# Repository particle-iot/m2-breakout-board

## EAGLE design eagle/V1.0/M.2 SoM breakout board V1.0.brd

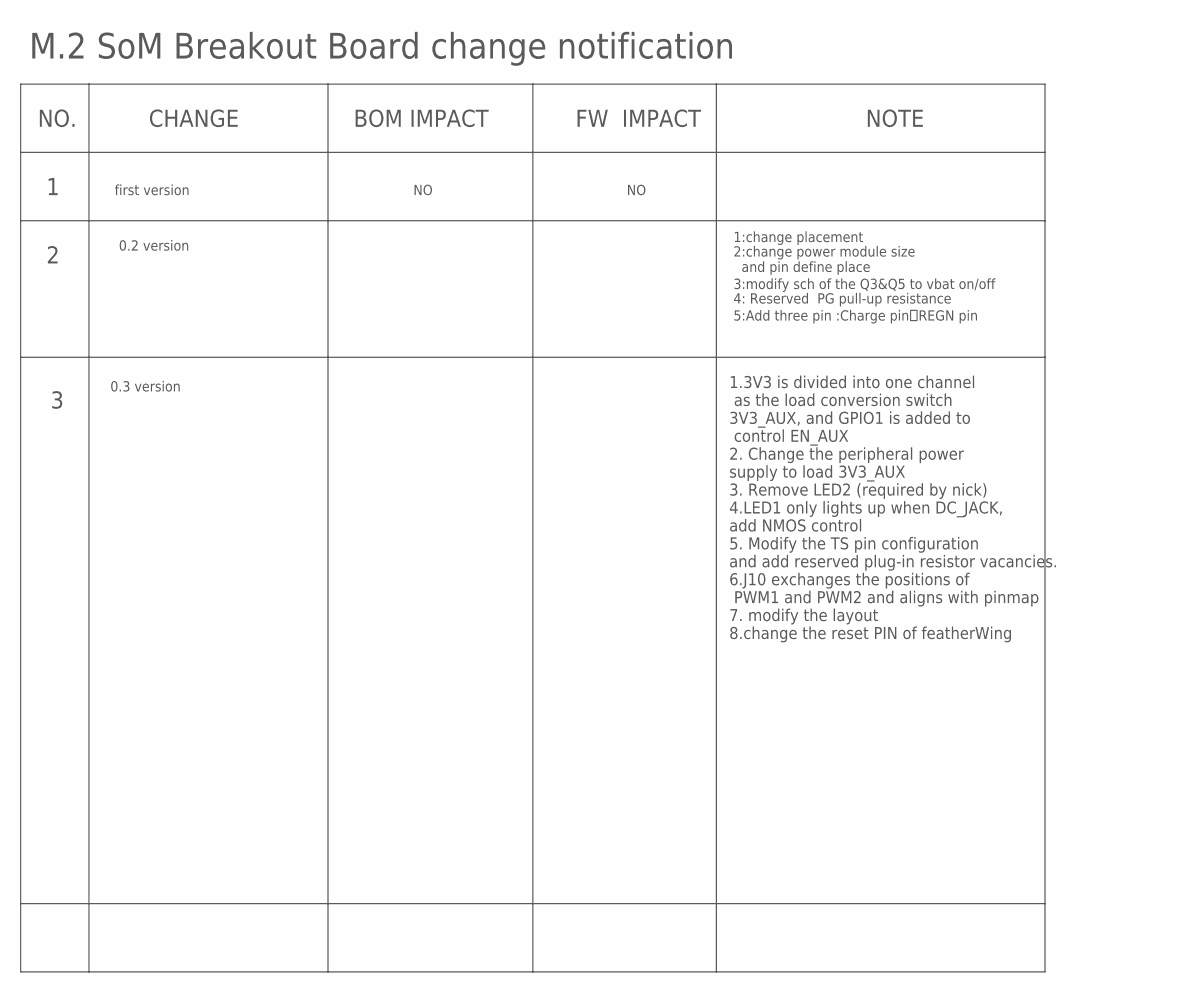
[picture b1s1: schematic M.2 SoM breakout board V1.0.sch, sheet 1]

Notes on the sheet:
NO.
CHANGE
BOM IMPACT
FW IMPACT
NOTE
first version
M.2 SoM Breakout Board change notification
0.2 version
1:change placement
3:modify sch of the Q3&Q5 to vbat on/off
5:Add three pin :Charge pin，REGN pin
2:change power module size and pin define place
4: Reserved PG pull-up resistance
0.3 version
1.3V3 is divided into one channel as the load conversion switch 3V3_AUX, and GPIO1 is added to control EN_AUX 2. Change the peripheral power supply to load 3V3_AUX 3. Remove LED2 (required by nick) 4.LED1 only lights up when DC_JACK, add NMOS control 5. Modify the TS pin configuration and add reser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

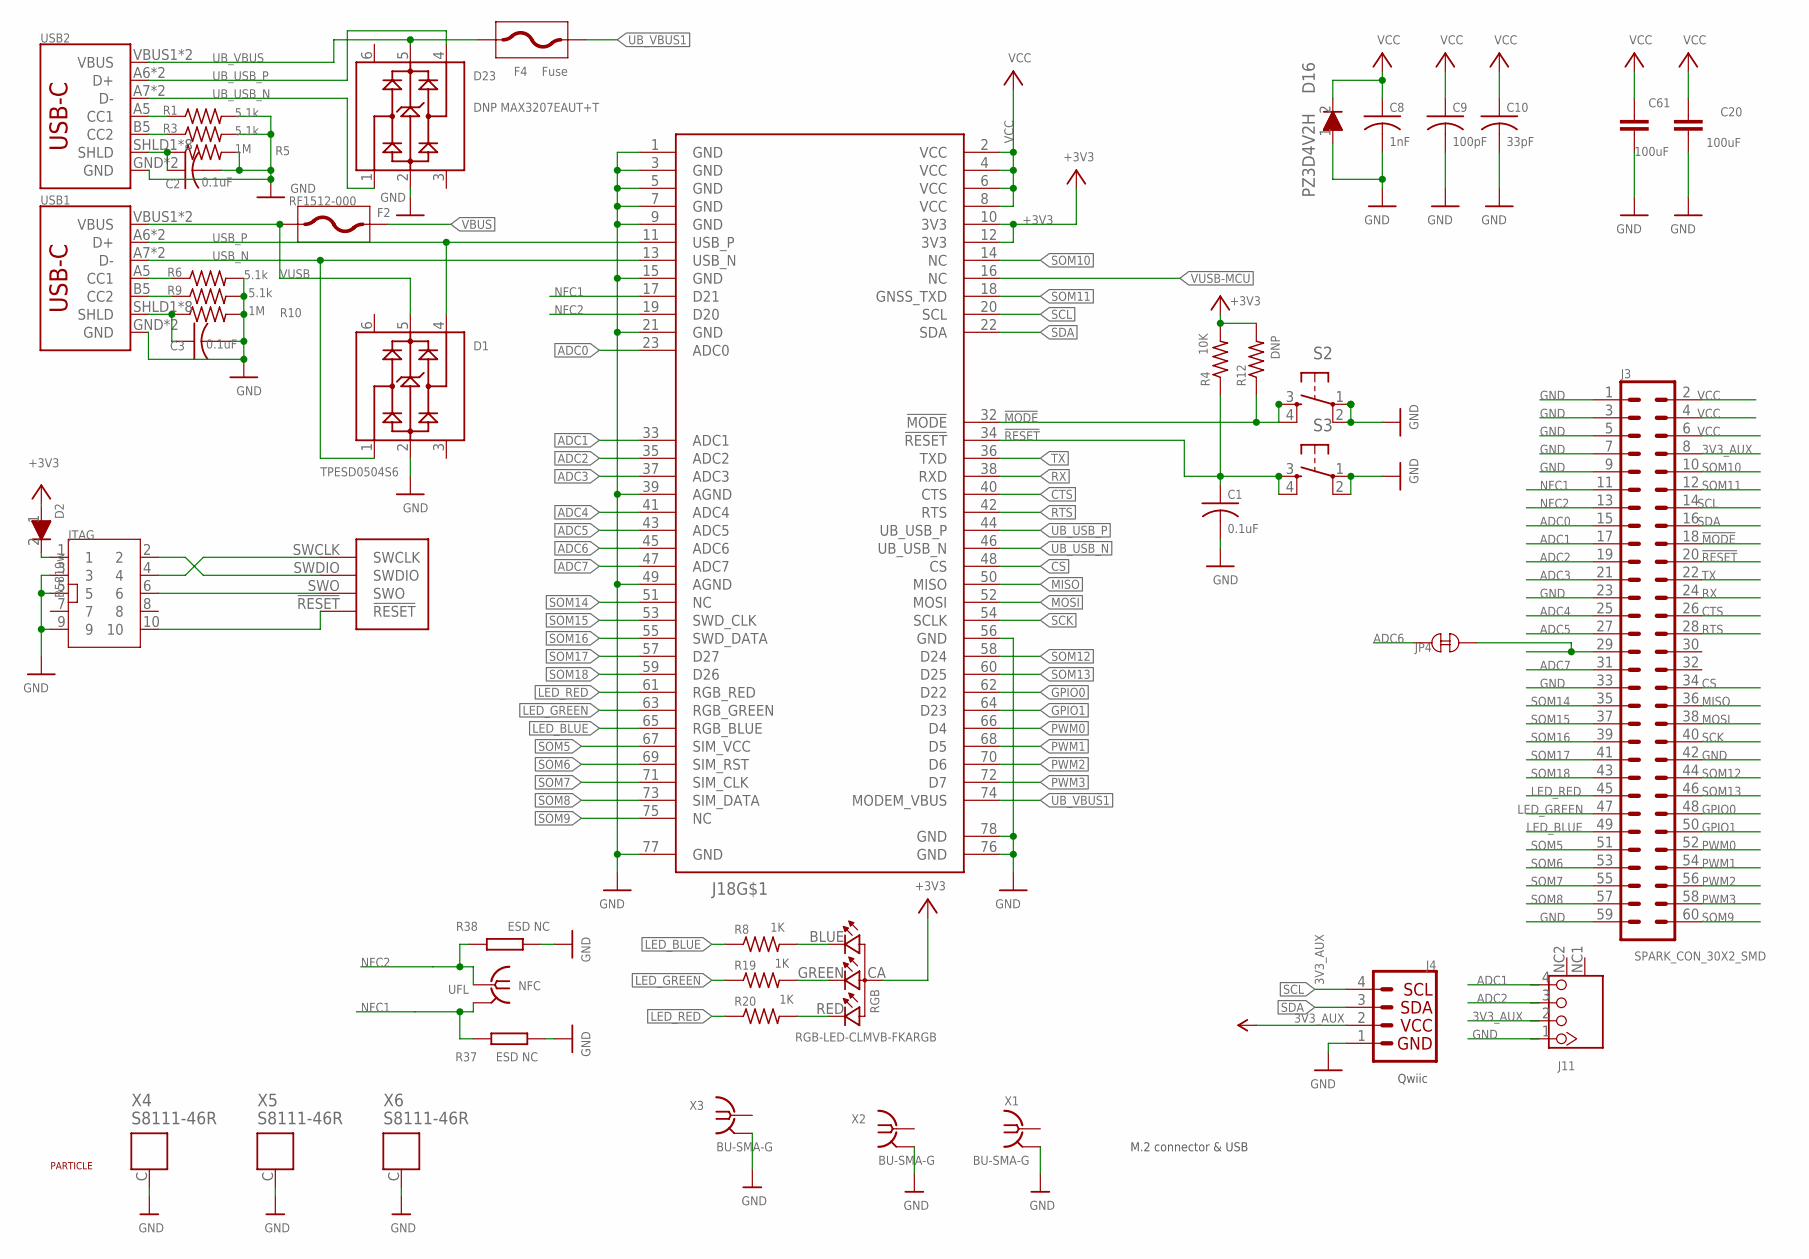
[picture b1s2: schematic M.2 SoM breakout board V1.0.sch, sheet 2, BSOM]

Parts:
C1, C2, C3: 0.1uF; C0402_B
C8: 1nF; C0402_B
C9: 100pF; C0402_B
C10: 33pF; C0402_B
C20, C61: 100uF; C1206K
D1: TPESD0504S6; SOT23-6
D2: B5819w; SOD-123
D16: PZ3D4V2H; SOD-323
D23: DNP MAX3207EAUT+T; SOT23-6
F2: RF1512-000; F0805
F4: Fuse; F0805
J3: SPARK_CON_30X2_SMD
J4: QWIIC_CONNECTORJS-1MM; 1X04_1MM_RA
J11: WAFER-HY2.0-4PWB; M.2-SOM-BREAKOUT-BOARD-V0.2-0228_WAFER-HY2.0-4PWB
J18: PARTICLE-STUDIOS_M_SERIES_M.2KEY; PARTICLE-STUDIOS_PARTICLE_M.2EKEY_3.65MM_DRILL
JP4: TP_SHORT
JTAG: CONN5X2; CONN5X2_1.27; MPN P6014A-M2GC-030-10
NFC: UFL; IPEX-20279-001E
R1, R3, R6, R9: 5.1k; R0402_B
R4: 10K; R0402_B
R5, R10: 1M; R0402_B
R8, R19, R20: 1K; R0402_B
R12: DNP; R0402_B
R37, R38: ESD NC; R-0402S
RGB: RGB-LED-CLMVB-FKARGB; PLCC4-2MM-RGB
S2, S3: TAC_SWITCH; TACTILE_SWITCH_4.2*3.2
U$6: PARTICLE-LOGO
USB1, USB2: USB_C16PIN; USB-C-16P
X1, X2, X3: BU-SMA-G
X4, X5, X6: S8111-46R

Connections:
3V3_AUX: J3.8, J4.2, J11.2; also elsewhere on the board
!MODE: J3.18, J18.32 (!MODE), R12.1, S2.3, S2.4
!RESET: C1.1, J3.20, J18.34 (!RESET), J18.!RESET, JTAG.10, R4.1, S3.3, S3.4; also elsewhere on the board
+3V3: D2.1, J18.10 (3V3), J18.12 (3V3), R4.2, R12.2, RGB.CA (1); also elsewhere on the board
ADC0: J3.15, J18.23 (ADC0); also elsewhere on the board
ADC1: J3.17, J11.4, J18.33 (ADC1); also elsewhere on the board
ADC2: J3.19, J11.3, J18.35 (ADC2); also elsewhere on the board
ADC3: J3.21, J18.37 (ADC3); also elsewhere on the board
ADC4: J3.25, J18.41 (ADC4); also elsewhere on the board
ADC5: J3.27, J18.43 (ADC5); also elsewhere on the board
ADC6: J18.45 (ADC6), JP4.2; also elsewhere on the board
ADC7: J3.31, J18.47 (ADC7)
CS: J3.34, J18.48 (CS); also elsewhere on the board
CTS: J3.26, J18.40 (CTS); also elsewhere on the board
GND: C1.2, C2.2, C3.2, C8.2, C9.2, C10.2, C20.2, C61.2, D1.2, D16.1, D23.2, J3.1, J3.3, J3.5, J3.7, J3.9, J3.23, J3.33, J3.42, J3.59, J4.1, J11.1, J18.1 (GND), J18.3 (GND), J18.5 (GND), J18.7 (GND), J18.9 (GND), J18.15 (GND), J18.21 (GND), J18.39 (AGND), J18.49 (AGND), J18.56 (GND), J18.76 (GND), J18.77 (GND), J18.78 (GND), JTAG.3, JTAG.5, JTAG.9, R1.2, R3.2, R5.2, R6.2, R9.2, R10.2, R37.2, R38.1, S2.1, S2.2, S3.1, S3.2, USB1.GND, USB1.GND2 (GND), USB2.GND, USB2.GND2 (GND), X1.2, X1.3 (2), X1.4 (2), X1.5 (2), X2.2, X2.3 (2), X2.4 (2), X2.5 (2), X3.2, X3.3 (2), X3.4 (2), X3.5 (2), X4.C, X5.C, X6.C; also elsewhere on the board
GPIO0: J3.48, J18.62 (D22); also elsewhere on the board
GPIO1: J3.50, J18.64 (D23); also elsewhere on the board
LED_BLUE: J3.49, J18.65 (RGB_BLUE), R8.1
LED_BLUE1: R8.2, RGB.BLUE (2)
LED_GREEN: J3.47, J18.63 (RGB_GREEN), R19.1
LED_GREEN1: R19.2, RGB.GREEN (3)
LED_RED: J3.45, J18.61 (RGB_RED), R20.1
LED_RED1: R20.2, RGB.RED (4)
MISO: J3.36, J18.50 (MISO); also elsewhere on the board
MOSI: J3.38, J18.52 (MOSI); also elsewhere on the board
unnamed: R1.1, USB2.A5 (CC1)
unnamed: R3.1, USB2.B5 (CC2)
unnamed: C2.1, R5.1, USB2.SHLD1 (SHLD), USB2.SHLD2 (SHLD), USB2.SHLD3 (SHLD), USB2.SHLD4 (SHLD), USB2.SHLD5 (SHLD), USB2.SHLD6 (SHLD), USB2.SHLD7 (SHLD), USB2.SHLD8 (SHLD)
unnamed: R6.1, USB1.A5 (CC1)
unnamed: R9.1, USB1.B5 (CC2)
unnamed: D2.2, JTAG.1
unnamed: C3.1, R10.1, USB1.SHLD1 (SHLD), USB1.SHLD2 (SHLD), USB1.SHLD3 (SHLD), USB1.SHLD4 (SHLD), USB1.SHLD5 (SHLD), USB1.SHLD6 (SHLD), USB1.SHLD7 (SHLD), USB1.SHLD8 (SHLD)
unnamed: J3.29, JP4.1
NFC1: J3.11, J18.17 (D21), NFC.2@1 (GND), NFC.2@2 (GND), R37.1
NFC2: J3.13, J18.19 (D20), NFC.1, R38.2
PWM0: J3.52, J18.66 (D4); also elsewhere on the board
PWM1: J3.54, J18.68 (D5); also elsewhere on the board
PWM2: J3.56, J18.70 (D6); also elsewhere on the board
PWM3: J3.58, J18.72 (D7); also elsewhere on the board
RTS: J3.28, J18.42 (RTS)
RX: J3.24, J18.38 (RXD); also elsewhere on the board
SCK: J3.40, J18.54 (SCLK); also elsewhere on the board
SCL: J3.14, J4.4, J18.20 (SCL); also elsewhere on the board
SDA: J3.16, J4.3, J18.22 (SDA); also elsewhere on the board
SOM5: J3.51, J18.67 (SIM_VCC)
SOM6: J3.53, J18.69 (SIM_RST)
SOM7: J3.55, J18.71 (SIM_CLK)
SOM8: J3.57, J18.73 (SIM_DATA)
SOM9: J3.60, J18.75 (NC)
SOM10: J3.10, J18.14 (NC)
SOM11: J3.12, J18.18 (GNSS_TXD)
SOM12: J3.44, J18.58 (D24)
SOM13: J3.46, J18.60 (D25)
SOM14: J3.35, J18.51 (NC)
SOM15: J3.37, J18.53 (SWD_CLK)
SOM16: J3.39, J18.55 (SWD_DATA)
SOM17: J3.41, J18.57 (D27)
SOM18: J3.43, J18.59 (D26)
SWCLK: J18.SWCLK, JTAG.4
SWDIO: J18.SWDIO, JTAG.2
SWO: J18.SWO, JTAG.6
TX: J3.22, J18.36 (TXD); also elsewhere on the board
UB_USB_N: D23.1, J18.46 (UB_USB_N), USB2.A7 (D-), USB2.B7 (D-)
UB_USB_P: D23.4, J18.44 (UB_USB_P), USB2.A6 (D+), USB2.B6 (D+)
UB_VBUS: D23.5, F4.P$2 (2), USB2.VBUS1 (VBUS), USB2.VBUS2 (VBUS)
UB_VBUS1: F4.P$1 (1), J18.74 (MODEM_VBUS)
USB_N: D1.1, J18.13 (USB_N), USB1.A7 (D-), USB1.B7 (D-)
USB_P: D1.4, J18.11 (USB_P), USB1.A6 (D+), USB1.B6 (D+)
VBUS: F2.P$2 (2); also elsewhere on the board
VCC: C8.1, C9.1, C10.1, C20.1, C61.1, D16.2, J3.2, J3.4, J3.6, J18.2 (VCC), J18.4 (VCC), J18.6 (VCC), J18.8 (VCC); also elsewhere on the board
VUSB: D1.5, F2.P$1 (1), USB1.VBUS1 (VBUS), USB1.VBUS2 (VBUS)
VUSB-MCU: J18.16 (NC); also elsewhere on the board

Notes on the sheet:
Qwiic
M.2 connector & USB

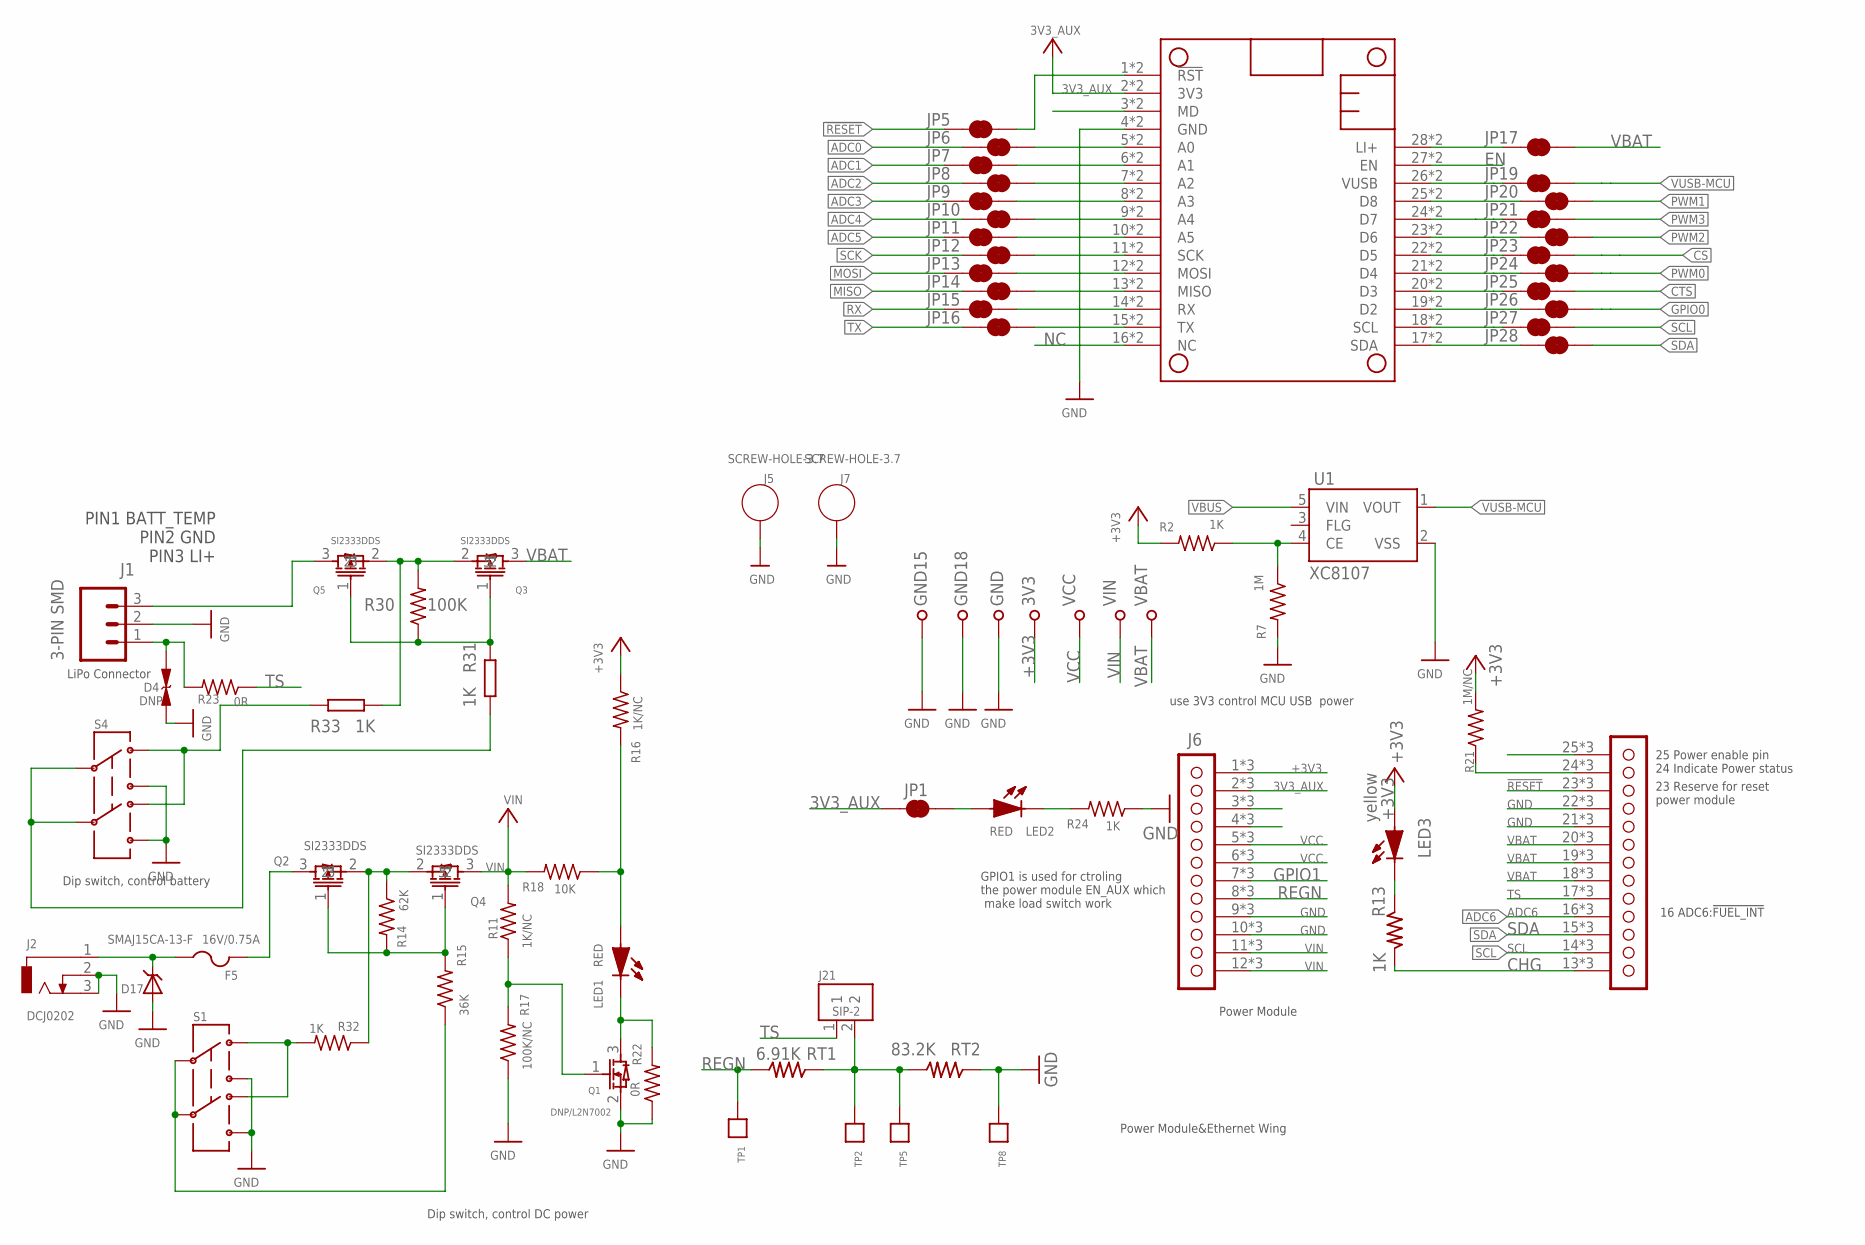
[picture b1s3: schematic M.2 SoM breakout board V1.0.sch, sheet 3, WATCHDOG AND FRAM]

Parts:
3V3: TP-S2751-46R; S2751-46R
D4: DNP; C0402
D17: SMAJ15CA-13-F; SMADIODE
F5: 16V/0.75A; 1812
GND, GND15, GND18: TP-S2751-46R; S2751-46R
J1: 3-PIN SMD; JST-3-SMD
J2: DCJ0202
J5, J7: SCREW-HOLE-3.7
J6: M.2-SOM-BREAKOUT-BOARD-V0.3_M.2-SOM-BREAKOUT-BOAR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; M.2-SOM-BREAKOUT-BOARD-V0.3_M.2-SOM-BREAKOUT-BOARD-V0.2-022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
J21: SIP-2
JP1, JP5, JP6, JP7, JP8, JP9, JP10, JP11, JP12, JP13, JP14, JP15, JP16, JP17, JP19, JP20, JP21, JP22, JP23, JP24, JP25, JP26, JP27, JP28: JUMPER-SMT_2_NC_TRACE_NO-SILK; SMT-JUMPER_2_NC_TRACE_NO-SILK
LED1, LED2: RED; LED0603
LED3: yellow; LED0603
MS1: PARTICLE_MESH_SMTDUAL; FEATHERWING_SMT2
Q1: DNP/L2N7002; SOT323
Q2, Q3, Q4, Q5: SI2333DDS; SOT-23
R2, R24, R32: 1K; R0402_B
R7: 1M; R0402_B
R11, R16: 1K/NC; R0402_B
R13, R31, R33: 1K; R-0402S
R14: 62K; R0402_B
R15: 36K; R0402_B
R17: 100K/NC; R0402_B
R18: 10K; R0402_B
R21: 1M/NC; R0402_B
R22, R23: 0R; R0402_B
R30: 100K; R0603_P
RT1: 6.91K; R-0603A
RT2: 83.2K; R-0603A
S1, S4: SWITCH-DPDT; SWITCH-2.5X3.2-6
TP1, TP2, TP5, TP8: TPTPEB; TPEB
U1: XC8107; SOT25
VBAT: TP-S2751-46R; S2751-46R
VCC: TP-S2751-46R; S2751-46R
VIN: TP-S2751-46R; S2751-46R

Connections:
3V3_AUX: J6.2 (3V3), J6.@2 (3V3), J6.P$2 (3V3), JP1.1, MS1.2 (3V3), MS1.2' (3V3); also elsewhere on the board
!RESET: J6.23 (!RST), J6.@23 (!RST), J6.P$23 (!RST), JP5.1; also elsewhere on the board
+3V3: 3V3.1, J6.1 (3V3), J6.@1 (3V3), J6.P$1 (3V3), LED3.1 (A), R2.2, R16.1, R21.2; also elsewhere on the board
ADC0: JP6.1; also elsewhere on the board
ADC1: JP7.1; also elsewhere on the board
ADC2: JP8.1; also elsewhere on the board
ADC3: JP9.1; also elsewhere on the board
ADC4: JP10.1; also elsewhere on the board
ADC5: JP11.1; also elsewhere on the board
ADC6: J6.16 (!FUEL-INT), J6.@16 (!FUEL-INT), J6.P$16 (!FUEL-INT); also elsewhere on the board
CHG: J6.13 (CHG), J6.@13 (CHG), J6.P$13 (CHG), R13.2
CS: JP23.2; also elsewhere on the board
CTS: JP25.2; also elsewhere on the board
EN: MS1.27 (EN), MS1.27' (EN)
GND: D4.1, D17.A, GND.1, GND15.1, GND18.1, J1.2, J2.2, J2.3, J5.P$1, J6.9 (GND), J6.10 (GND), J6.21 (GND), J6.22 (GND), J6.@9 (GND), J6.@10 (GND), J6.@21 (GND), J6.@22 (GND), J6.P$9 (GND), J6.P$10 (GND), J6.P$21 (GND), J6.P$22 (GND), J7.P$1, MS1.4 (GND), MS1.4' (GND), Q1.2, R7.2, R17.1, R22.1, R24.1, RT2.1, S1.3, S1.6, S4.3, S4.6, TP8.1, U1.2 (VSS); also elsewhere on the board
GPIO0: JP26.2; also elsewhere on the board
GPIO1: J6.7 (REGN), J6.@7 (REGN), J6.P$7 (REGN); also elsewhere on the board
LI+: JP17.1, MS1.28 (LI+), MS1.28' (LI+)
MISO: JP14.1; also elsewhere on the board
MOSI: JP13.1; also elsewhere on the board
unnamed: MS1.3 (MD), MS1.3' (MD)
unnamed: R2.1, R7.1, U1.4 (CE)
unnamed: Q2.2, Q4.2, R14.1, R32.1
unnamed: F5.2, Q2.3
unnamed: LED3.2 (K), R13.1
unnamed: J21.2, RT1.1, RT2.2, TP2.1, TP5.1
unnamed: LED2.2 (K), R24.2
unnamed: JP21.1, MS1.24 (D7), MS1.24' (D7)
unnamed: Q2.1, Q4.1, R14.2, R15.2
unnamed: LED1.1 (A), R16.2, R18.1
unnamed: Q1.1, R11.1, R17.2
unnamed: R33.1, S4.1, S4.4
unnamed: JP6.2, MS1.5 (A0), MS1.5' (A0)
unnamed: J6.24 (PG), J6.@24 (PG), J6.P$24 (PG), R21.1
unnamed: JP7.2, MS1.6 (A1), MS1.6' (A1)
unnamed: JP8.2, MS1.7 (A2), MS1.7' (A2)
unnamed: JP9.2, MS1.8 (A3), MS1.8' (A3)
unnamed: JP10.2, MS1.9 (A4), MS1.9' (A4)
unnamed: JP11.2, MS1.10 (A5), MS1.10' (A5)
unnamed: JP12.2, MS1.11 (SCK), MS1.11' (SCK)
unnamed: JP13.2, MS1.12 (MOSI), MS1.12' (MOSI)
unnamed: JP14.2, MS1.13 (MISO), MS1.13' (MISO)
unnamed: JP15.2, MS1.14 (RX), MS1.14' (RX)
unnamed: JP16.2, MS1.15 (TX), MS1.15' (TX)
unnamed: R32.2, S1.1, S1.4
unnamed: JP28.1, MS1.17 (SDA), MS1.17' (SDA)
unnamed: JP27.1, MS1.18 (SCL), MS1.18' (SCL)
unnamed: LED1.2 (K), Q1.3, R22.2
unnamed: JP26.1, MS1.19 (D2), MS1.19' (D2)
unnamed: JP25.1, MS1.20 (D3), MS1.20' (D3)
unnamed: JP24.1, MS1.21 (D4), MS1.21' (D4)
unnamed: JP23.1, MS1.22 (D5), MS1.22' (D5)
unnamed: JP22.1, MS1.23 (D6), MS1.23' (D6)
unnamed: JP20.1, MS1.25 (D8), MS1.25' (D8)
unnamed: J6.3 (5DC), J6.@3 (5DC), J6.P$3 (5DC)
unnamed: D17.C, F5.1, J2.1
unnamed: JP5.2, MS1.1 (!RST), MS1.1' (!RST)
unnamed: JP1.2, LED2.1 (A)
unnamed: J6.25 (ENABLE), J6.@25 (ENABLE), J6.P$25 (ENABLE)
unnamed: R15.1, S1.2, S1.5
unnamed: J1.3, Q5.3
unnamed: J6.4 (5DC), J6.@4 (5DC), J6.P$4 (5DC)
unnamed: D4.2, J1.1, R23.2
unnamed: Q3.2, Q5.2, R30.2, R33.2
unnamed: Q3.1, Q5.1, R30.1, R31.1
unnamed: R31.2, S4.2, S4.5
NC: MS1.16 (NC), MS1.16' (NC)
PWM0: JP24.2; also elsewhere on the board
PWM1: JP20.2; also elsewhere on the board
PWM2: JP22.2; also elsewhere on the board
PWM3: JP21.2; also elsewhere on the board
REGN: J6.8 (NC), J6.@8 (NC), J6.P$8 (NC), RT1.2, TP1.1
RX: JP15.1; also elsewhere on the board
SCK: JP12.1; also elsewhere on the board
SCL: J6.14 (SCL), J6.@14 (SCL), J6.P$14 (SCL), JP27.2; also elsewhere on the board
SDA: J6.15 (SDA), J6.@15 (SDA), J6.P$15 (SDA), JP28.2; also elsewhere on the board
TS: J6.17 (TS), J6.@17 (TS), J6.P$17 (TS), J21.1, R23.1
TX: JP16.1; also elsewhere on the board
V-USB: JP19.1, MS1.26 (VUSB), MS1.26' (VUSB)
VBAT: J6.18 (VBAT), J6.19 (VBAT), J6.20 (VBAT), J6.@18 (VBAT), J6.@19 (VBAT), J6.@20 (VBAT), J6.P$18 (VBAT), J6.P$19 (VBAT), J6.P$20 (VBAT), JP17.2, Q3.3, VBAT.1
VBUS: U1.5 (VIN); also elsewhere on the board
VCC: J6.5 (VCC), J6.6 (VCC), J6.@5 (VCC), J6.@6 (VCC), J6.P$5 (VCC), J6.P$6 (VCC), VCC.1; also elsewhere on the board
VIN: J6.11 (VIN), J6.12 (VIN), J6.@11 (VIN), J6.@12 (VIN), J6.P$11 (VIN), J6.P$12 (VIN), Q4.3, R11.2, R18.2, VIN.1
VUSB-MCU: JP19.2, U1.1 (VOUT); also elsewhere on the board

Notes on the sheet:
LiPo Connector
16 ADC6:!FUEL_INT
Power Module
Dip switch, control battery
Dip switch, control DC power
use 3V3 control MCU USB power
Power Module&Ethernet Wing
PIN1 BATT_TEMP PIN2 GND PIN3 LI+
24 Indicate Power status
25 Power enable pin
23 Reserve for reset power module
GPIO1 is used for ctroling the power module EN_AUX which make load switch work

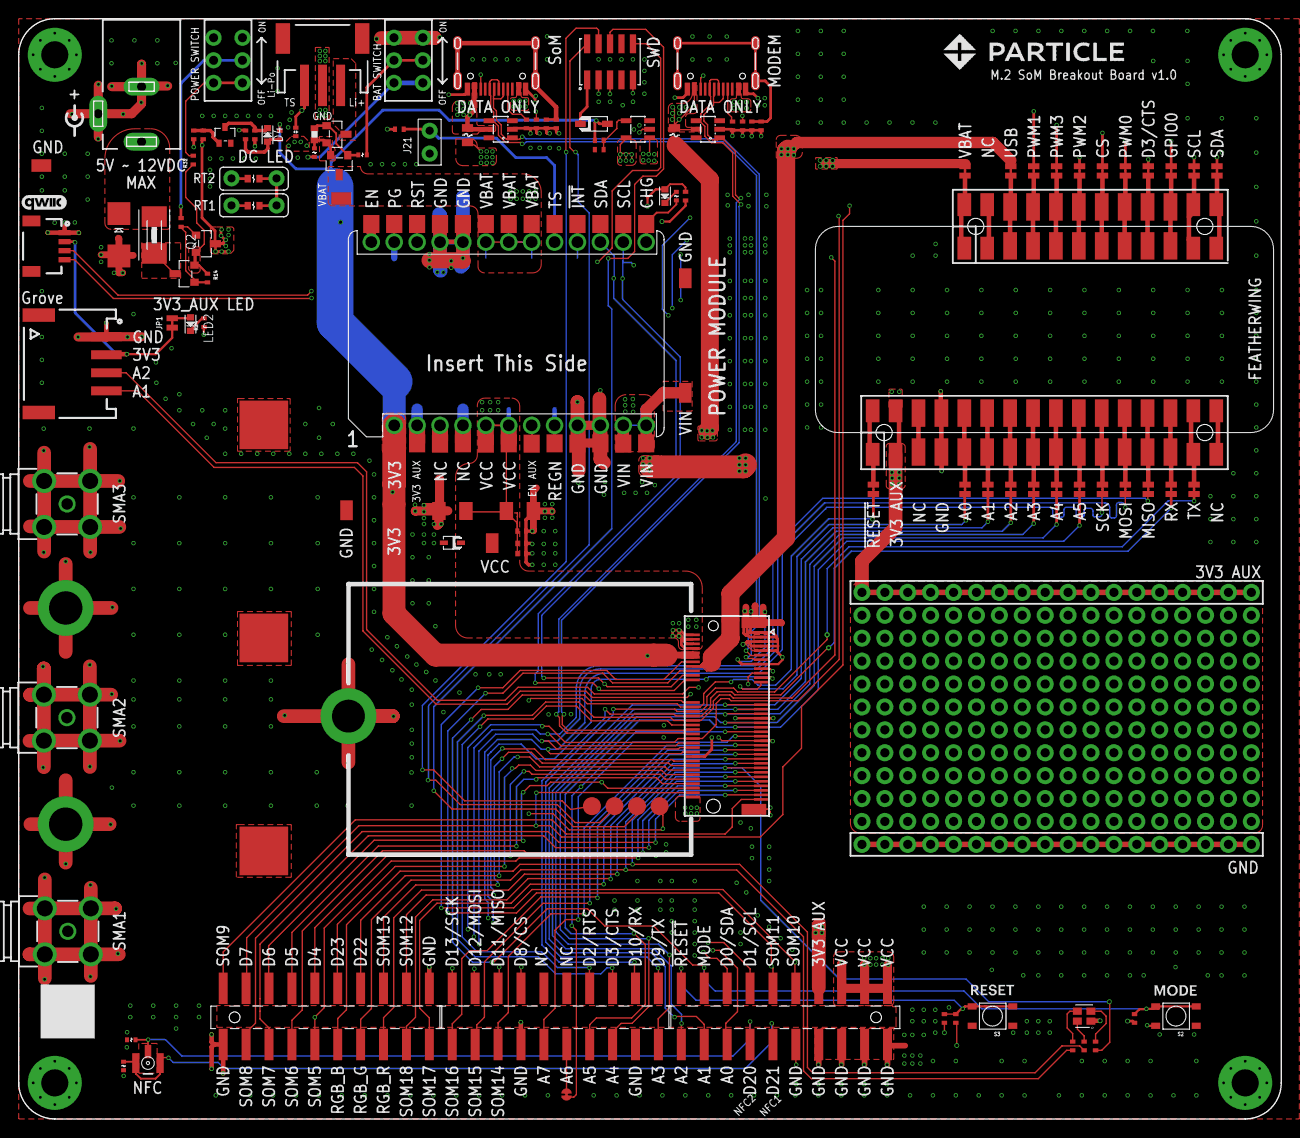
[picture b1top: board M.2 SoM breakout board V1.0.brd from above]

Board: 4 copper layers, 140.0 x 122.0 mm, 122 parts (1 on the bottom side), 127 nets.

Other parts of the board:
LOGO2: QWIIC_LOGO_5MM; QWIIC_5MM

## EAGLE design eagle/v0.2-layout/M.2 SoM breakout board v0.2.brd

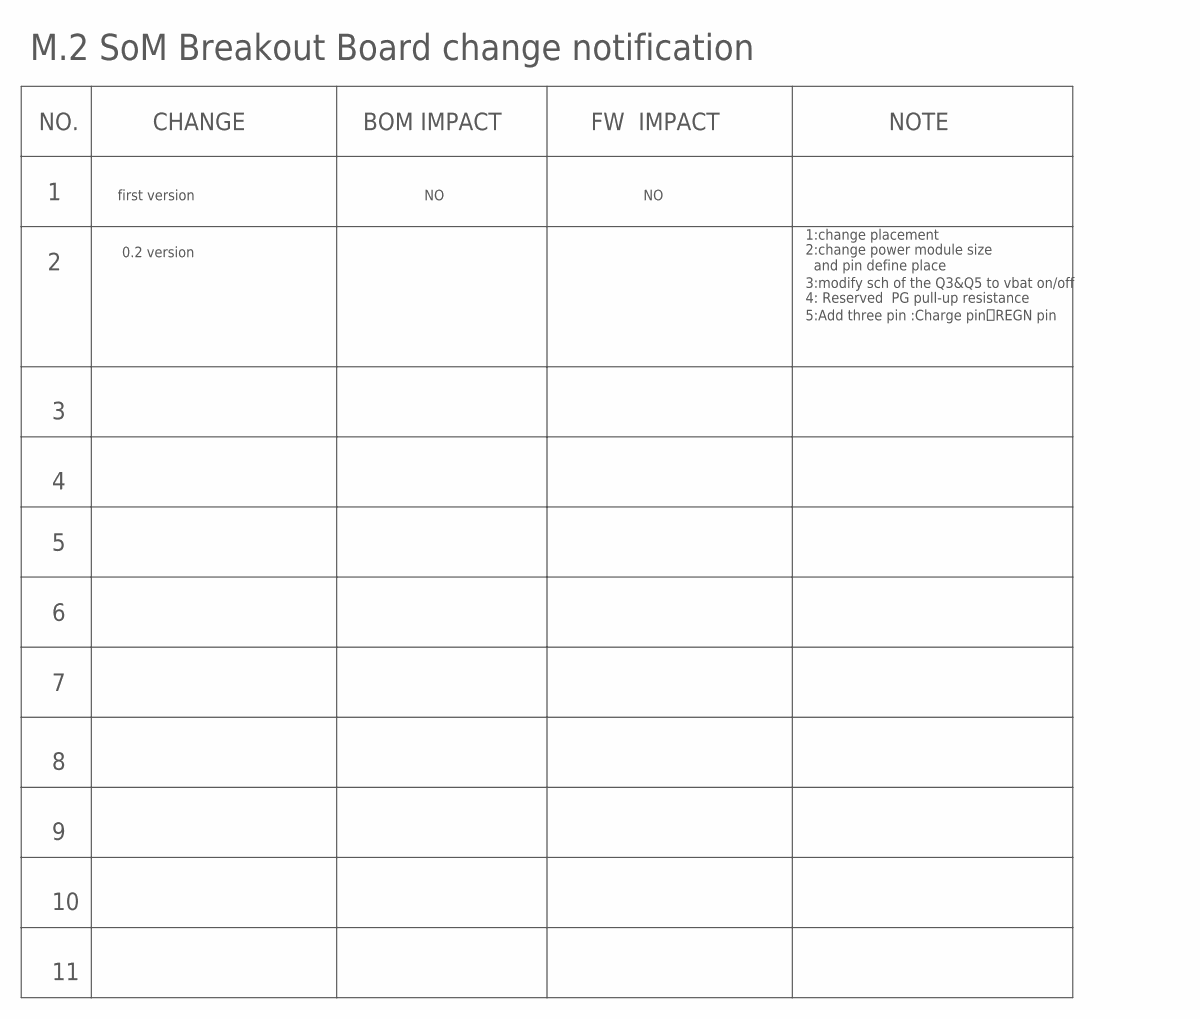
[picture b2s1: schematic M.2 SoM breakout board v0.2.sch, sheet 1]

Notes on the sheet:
NO.
CHANGE
BOM IMPACT
FW IMPACT
NOTE
first version
M.2 SoM Breakout Board change notification
0.2 version
1:change placement
3:modify sch of the Q3&Q5 to vbat on/off
5:Add three pin :Charge pin，REGN pin
2:change power module size and pin define place
4: Reserved PG pull-up resistance

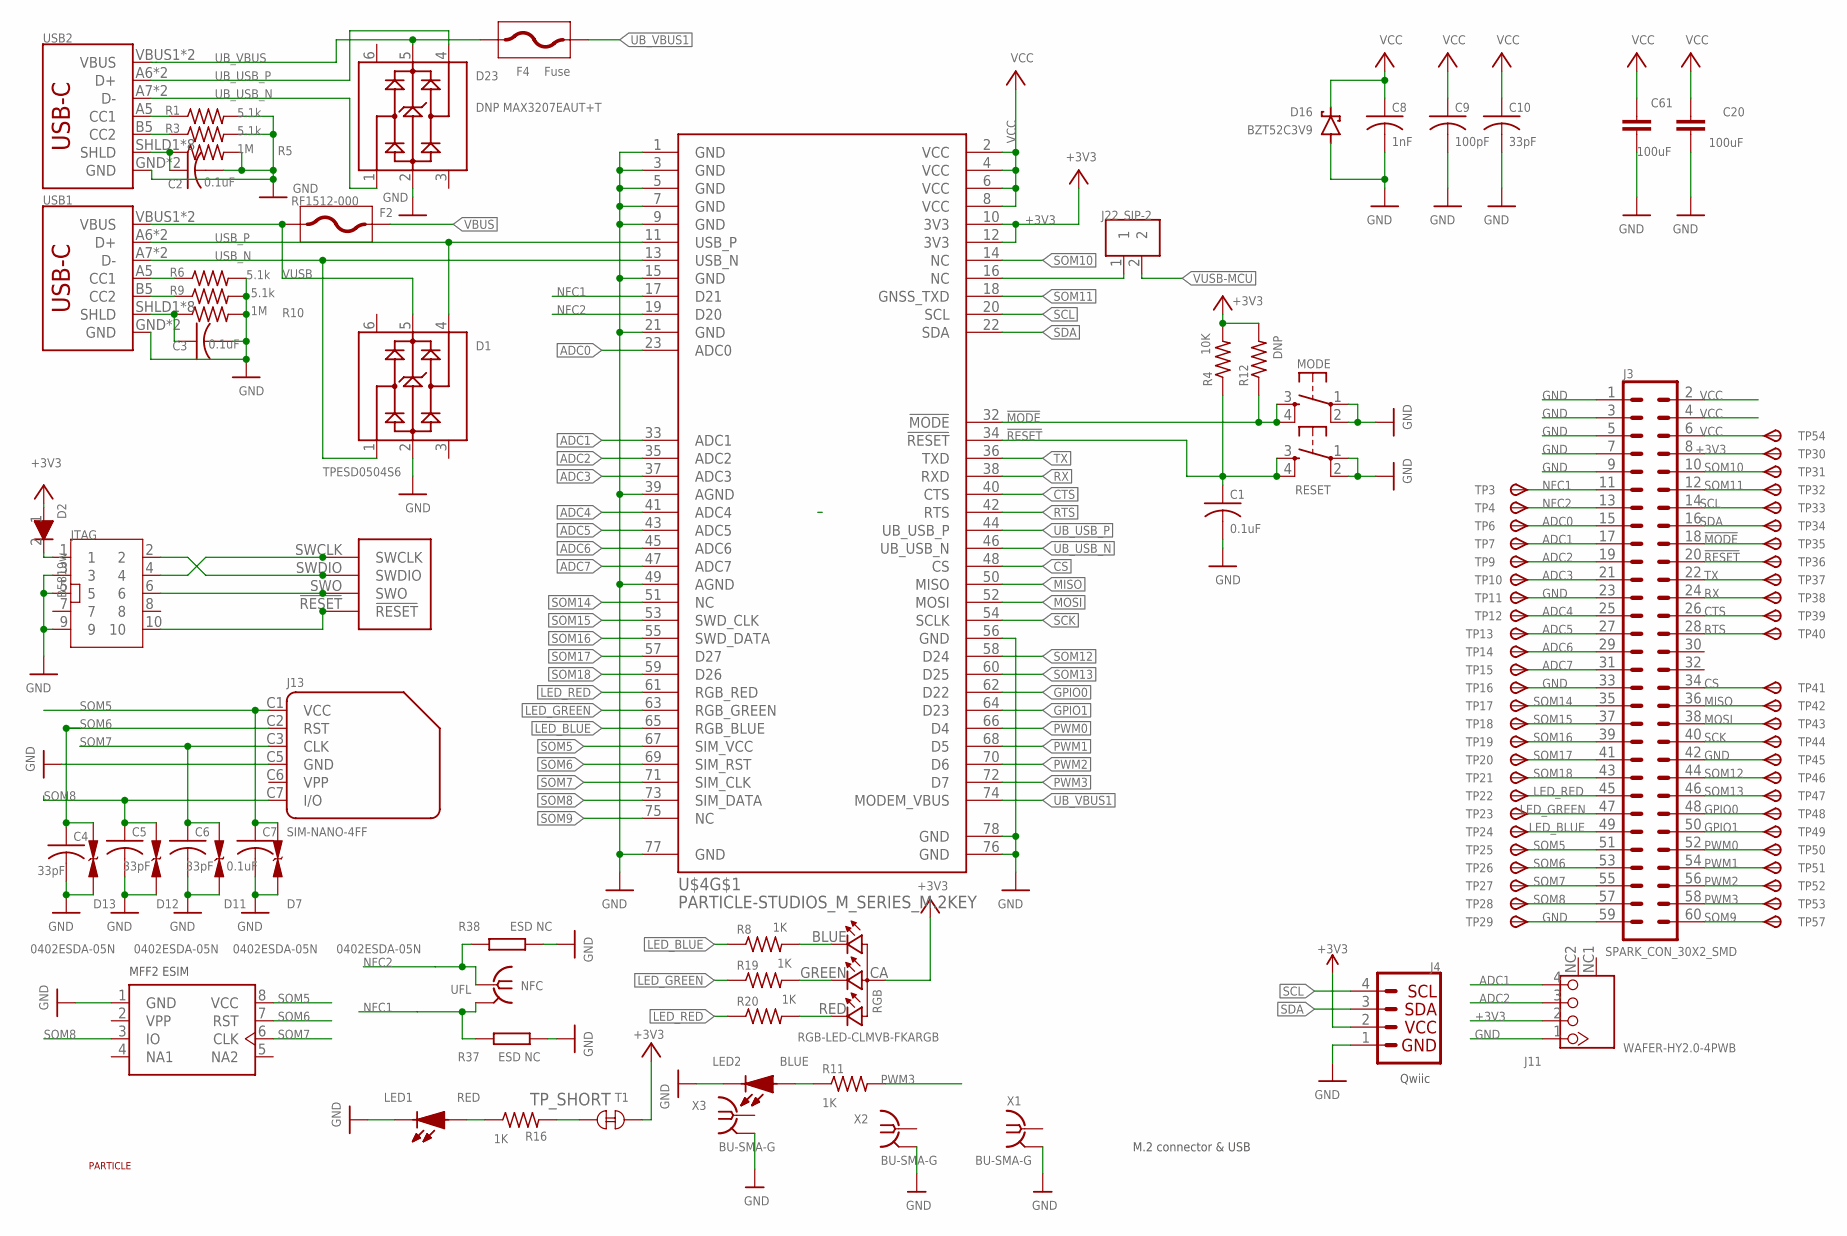
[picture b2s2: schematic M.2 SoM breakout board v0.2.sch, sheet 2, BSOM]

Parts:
C1, C2, C3, C7: 0.1uF; C0402_B
C4, C5, C6, C10: 33pF; C0402_B
C8: 1nF; C0402_B
C9: 100pF; C0402_B
C20, C61: 100uF; C1206K
D1: TPESD0504S6; SOT23-6
D2: B5819w; SOD-123
D7, D11, D12, D13: 0402ESDA-05N; C0402
D16: BZT52C3V9; SOD-123
D23: DNP MAX3207EAUT+T; SOT23-6
F2: RF1512-000; R1206
F4: Fuse; F0805
J3: SPARK_CON_30X2_SMD
J4: QWIIC_CONNECTORJS-1MM; 1X04_1MM_RA
J11: WAFER-HY2.0-4PWB
J13: SIM-NANO-4FF; GCT-SIM8100
J22: SIP-2
JTAG: CONN5X2; CONN5X2_1.27; MPN P6014A-M2GC-030-10
LED1: RED; LED0603
LED2: BLUE; LED0603
MODE: TAC_SWITCHSMD; TACTILE_SWITCH_SMD; MPN TS-1185A-025C
NFC: UFL; IPEX-20279-001E
R1, R3, R6, R9: 5.1k; R0402_B
R4: 10K; R0402_B
R5, R10: 1M; R0402_B
R8, R11, R16, R19, R20: 1K; R0402_B
R12: DNP; R0402_B
R37, R38: ESD NC; R-0402S
RESET: TAC_SWITCHSMD; TACTILE_SWITCH_SMD; MPN TS-1185A-025C
RGB: RGB-LED-CLMVB-FKARGB; PLCC4-2MM-RGB
T1: TP_SHORT
TP3, TP4, TP6, TP7, TP9, TP10, TP11, TP12, TP13, TP14, TP15, TP16, TP17, TP18, TP19, TP20, TP21, TP22, TP23, TP24, TP25, TP26, TP27, TP28, TP29, TP30, TP31, TP32, TP33, TP34, TP35, TP36, TP37, TP38, TP39, TP40, TP41, TP42, TP43, TP44, TP45, TP46, TP47, TP48, TP49, TP50, TP51, TP52, TP53, TP54, TP57: TPSB1,27; B1,27
U7: NC; MFF2
U$4: PARTICLE-STUDIOS_M_SERIES_M.2KEY; PARTICLE-STUDIOS_PARTICLE_M.2EKEY_3.65MM_DRILL
U$6: PARTICLE-LOGO
USB1, USB2: USB_C16PIN; USB-C-16P
X1, X2, X3: BU-SMA-G

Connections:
!MODE: J3.18, MODE.3, MODE.4, R12.1, TP35.TP, U$4.32 (!MODE)
!RESET: C1.1, J3.20, JTAG.10, R4.1, RESET.3, RESET.4, TP36.TP, U$4.34 (!RESET), U$4.!RESET; also elsewhere on the board
+3V3: D2.1, J3.8, J4.2, J11.2, R4.2, R12.2, RGB.CA (1), T1.1, TP30.TP, U$4.10 (3V3), U$4.12 (3V3); also elsewhere on the board
ADC0: J3.15, TP6.TP, U$4.23 (ADC0); also elsewhere on the board
ADC1: J3.17, J11.4, TP7.TP, U$4.33 (ADC1); also elsewhere on the board
ADC2: J3.19, J11.3, TP9.TP, U$4.35 (ADC2); also elsewhere on the board
ADC3: J3.21, TP10.TP, U$4.37 (ADC3); also elsewhere on the board
ADC4: J3.25, TP12.TP, U$4.41 (ADC4); also elsewhere on the board
ADC5: J3.27, TP13.TP, U$4.43 (ADC5); also elsewhere on the board
ADC6: J3.29, TP14.TP, U$4.45 (ADC6); also elsewhere on the board
ADC7: J3.31, TP15.TP, U$4.47 (ADC7); also elsewhere on the board
CS: J3.34, TP41.TP, U$4.48 (CS); also elsewhere on the board
CTS: J3.26, TP39.TP, U$4.40 (CTS)
GND: C1.2, C2.2, C3.2, C4.2, C5.2, C6.2, C7.2, C8.2, C9.2, C10.2, C20.2, C61.2, D1.2, D7.1, D11.1, D12.1, D13.1, D16.A, D23.2, J3.1, J3.3, J3.5, J3.7, J3.9, J3.23, J3.33, J3.42, J3.59, J4.1, J11.1, J13.C5 (GND), JTAG.3, JTAG.5, JTAG.9, LED1.2 (K), LED2.2 (K), MODE.1, MODE.2, R1.2, R3.2, R5.2, R6.2, R9.2, R10.2, R37.2, R38.1, RESET.1, RESET.2, TP11.TP, TP16.TP, TP29.TP, TP45.TP, U7.1 (GND), U$4.1 (GND), U$4.3 (GND), U$4.5 (GND), U$4.7 (GND), U$4.9 (GND), U$4.15 (GND), U$4.21 (GND), U$4.39 (AGND), U$4.49 (AGND), U$4.56 (GND), U$4.76 (GND), U$4.77 (GND), U$4.78 (GND), USB1.GND, USB1.GND2 (GND), USB2.GND, USB2.GND2 (GND), X1.2, X1.3 (2), X1.4 (2), X1.5 (2), X2.2, X2.3 (2), X2.4 (2), X2.5 (2), X3.2, X3.3 (2), X3.4 (2), X3.5 (2); also elsewhere on the board
GPIO0: J3.48, TP48.TP, U$4.62 (D22); also elsewhere on the board
GPIO1: J3.50, TP49.TP, U$4.64 (D23); also elsewhere on the board
LED_BLUE: J3.49, R8.1, TP24.TP, U$4.65 (RGB_BLUE)
LED_BLUE1: R8.2, RGB.BLUE (2)
LED_GREEN: J3.47, R19.1, TP23.TP, U$4.63 (RGB_GREEN)
LED_GREEN1: R19.2, RGB.GREEN (3)
LED_RED: J3.45, R20.1, TP22.TP, U$4.61 (RGB_RED)
LED_RED1: R20.2, RGB.RED (4)
MISO: J3.36, TP42.TP, U$4.50 (MISO); also elsewhere on the board
MOSI: J3.38, TP43.TP, U$4.52 (MOSI); also elsewhere on the board
unnamed: R1.1, USB2.A5 (CC1)
unnamed: R3.1, USB2.B5 (CC2)
unnamed: C2.1, R5.1, USB2.SHLD1 (SHLD), USB2.SHLD2 (SHLD), USB2.SHLD3 (SHLD), USB2.SHLD4 (SHLD), USB2.SHLD5 (SHLD), USB2.SHLD6 (SHLD), USB2.SHLD7 (SHLD), USB2.SHLD8 (SHLD)
unnamed: R6.1, USB1.A5 (CC1)
unnamed: R9.1, USB1.B5 (CC2)
unnamed: D2.2, JTAG.1
unnamed: C3.1, R10.1, USB1.SHLD1 (SHLD), USB1.SHLD2 (SHLD), USB1.SHLD3 (SHLD), USB1.SHLD4 (SHLD), USB1.SHLD5 (SHLD), USB1.SHLD6 (SHLD), USB1.SHLD7 (SHLD), USB1.SHLD8 (SHLD)
unnamed: LED1.1 (A), R16.1
unnamed: LED2.1 (A), R11.1
unnamed: R16.2, T1.2
NFC1: J3.11, NFC.2@1 (GND), NFC.2@2 (GND), R37.1, TP3.TP, U$4.17 (D21)
NFC2: J3.13, NFC.1, R38.2, TP4.TP, U$4.19 (D20)
PWM0: J3.52, TP50.TP, U$4.66 (D4); also elsewhere on the board
PWM1: J3.54, TP51.TP, U$4.68 (D5); also elsewhere on the board
PWM2: J3.56, TP52.TP, U$4.70 (D6); also elsewhere on the board
PWM3: J3.58, R11.2, TP53.TP, U$4.72 (D7); also elsewhere on the board
RTS: J3.28, TP40.TP, U$4.42 (RTS)
RX: J3.24, TP38.TP, U$4.38 (RXD); also elsewhere on the board
SCK: J3.40, TP44.TP, U$4.54 (SCLK); also elsewhere on the board
SCL: J3.14, J4.4, TP33.TP, U$4.20 (SCL); also elsewhere on the board
SDA: J3.16, J4.3, TP34.TP, U$4.22 (SDA); also elsewhere on the board
SOM5: C7.1, D7.2, J3.51, J13.C1 (VCC), TP25.TP, U7.8 (VCC), U$4.67 (SIM_VCC)
SOM6: C4.1, D13.2, J3.53, J13.C2 (RST), TP26.TP, U7.7 (RST), U$4.69 (SIM_RST)
SOM7: C6.1, D11.2, J3.55, J13.C3 (CLK), TP27.TP, U7.6 (CLK), U$4.71 (SIM_CLK)
SOM8: C5.1, D12.2, J3.57, J13.C7 (I/O), TP28.TP, U7.3 (IO), U$4.73 (SIM_DATA)
SOM9: J3.60, TP57.TP, U$4.75 (NC)
SOM10: J3.10, TP31.TP, U$4.14 (NC)
SOM11: J3.12, TP32.TP, U$4.18 (GNSS_TXD)
SOM12: J3.44, TP46.TP, U$4.58 (D24)
SOM13: J3.46, TP47.TP, U$4.60 (D25)
SOM14: J3.35, TP17.TP, U$4.51 (NC)
SOM15: J3.37, TP18.TP, U$4.53 (SWD_CLK)
SOM16: J3.39, TP19.TP, U$4.55 (SWD_DATA)
SOM17: J3.41, TP20.TP, U$4.57 (D27); also elsewhere on the board
SOM18: J3.43, TP21.TP, U$4.59 (D26); also elsewhere on the board
SWCLK: JTAG.4, U$4.SWCLK
SWDIO: JTAG.2, U$4.SWDIO
SWO: JTAG.6, U$4.SWO
TX: J3.22, TP37.TP, U$4.36 (TXD); also elsewhere on the board
UB_USB_N: D23.1, U$4.46 (UB_USB_N), USB2.A7 (D-), USB2.B7 (D-)
UB_USB_P: D23.4, U$4.44 (UB_USB_P), USB2.A6 (D+), USB2.B6 (D+)
UB_VBUS: D23.5, F4.P$2 (2), USB2.VBUS1 (VBUS), USB2.VBUS2 (VBUS)
UB_VBUS1: F4.P$1 (1), U$4.74 (MODEM_VBUS)
USB_N: D1.1, U$4.13 (USB_N), USB1.A7 (D-), USB1.B7 (D-)
USB_P: D1.4, U$4.11 (USB_P), USB1.A6 (D+), USB1.B6 (D+)
VBUS: F2.2; also elsewhere on the board
VCC: C8.1, C9.1, C10.1, C20.1, C61.1, D16.C, J3.2, J3.4, J3.6, TP54.TP, U$4.2 (VCC), U$4.4 (VCC), U$4.6 (VCC), U$4.8 (VCC); also elsewhere on the board
VPP: U7.2 (VPP)
VUSB: D1.5, F2.1, USB1.VBUS1 (VBUS), USB1.VBUS2 (VBUS)
VUSB-MCU: J22.2; also elsewhere on the board
VUSBMCU: J22.1, U$4.16 (NC)

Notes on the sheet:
Qwiic
MFF2 ESIM
M.2 connector & USB

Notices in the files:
parts and their libraries:
SparkFun-Retired: Licensing: Creative Commons ShareAlike 4.0 International - https://creativecommons.org/licenses/by-sa/4.0
